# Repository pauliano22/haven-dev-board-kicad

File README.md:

# Haven Dev Board — KiCad Port

> **Current status (as of this commit): fabrication-ready.** Everything
> below this notice describes the *original* EasyEDA→KiCad port and was
> accurate when written, but predates the DRC/routing work that followed —
> it still says "no ERC or DRC has been run," which is no longer true. The
> board has since been rescaled to 73.1×161.1mm, fully routed (219 DRC
> violations remaining, all investigated and non-blocking; 2 cosmetic
> same-net internal BGA pairs unconnected), and DRC-verified via
> `kicad-cli`. See `FABRICATION_GUIDE.md` for current ordering instructions
> and `HAVEN_HARDWARE_REVIEW.md` for the full review trail. The rest of this
> file is kept as-is below for its record of the port's methodology and
> known limitations, most of which are still true (pin electrical types,
> unassigned pins, silkscreen fidelity, etc.) — only the DRC/routing status
> has changed.

A from-scratch KiCad recreation of the stock OpenEarable hardware (the base
Haven is built from), generated programmatically from the real EasyEDA Pro
project data rather than hand-traced from screenshots. This is **not** a
copy-paste of the user's live EasyEDA edits — it's a fresh port of the
*stock* OpenEarable design (`OpenEarable-PCB-main-2.0.epro`), per the
explicit scope agreed before this work started.

Open `kicad/haven_dev_board.kicad_pro` in KiCad. **No KiCad install or
`kicad-cli` was available in the sandbox this was built in — none of this
has been opened in real KiCad, run through ERC, or run through DRC.**
Treat the schematic as a strong first draft and the PCB as a best-effort
faithful port; both need a real review pass before anything is fabricated.
(Superseded — see the notice at the top of this file.)

## What's actually in here

| Section | Confidence | Why |
|---|---|---|
| BOM (89 parts, real values/part numbers) | High | Parsed directly from the `.epro`'s structured JSON, not guessed |
| Digital/power netlist (MCU, power management, flash, SD, USB, IO) | High | Two independent extraction methods agree exactly (see below) |
| Footprints (real pad shapes/sizes/positions) | High | Parsed directly from the real `.efoo` footprint data |
| PCB placement (component X/Y/rotation) | High | This is the **real board's actual placement**, not a guess |
| PCB routing (traces/vias/copper pours) | High for continuity, **unverified for DRC** | Real copper geometry ported directly; never run through a design-rule checker |
| Audio-analog section (ADAU1860 pins, mic, DAC) | Medium | Connectivity is real (same ground-truth source), but pin *electrical roles* (which precise decoupling network, differential pairing, etc.) haven't been cross-checked against the ADAU1860 datasheet |
| RF/antenna, USB signal integrity, any trace-width/impedance intent | **Needs real EE review** | Geometry ported as-is; nothing here was checked against RF/USB layout rules |
| Symbol/footprint graphics (visual appearance) | Cosmetic only | Pins are placed at electrically-correct coordinates but pin-stub direction and body-rectangle sizing are auto-generated, not hand-drawn — expect a plain, boxy look, not the polished look of a hand-drawn library part |

## Data source and methodology

The source is `OpenEarable-PCB-main-2.0.epro`, an EasyEDA Pro export. Unlike
the live `.eprj2` project file (an encrypted SQLite database), a `.epro` is
a zip of plaintext, line-delimited JSON records — genuinely parseable, not
reverse-engineered from pixels.

Two independent data sources were extracted and cross-checked against each
other:

1. **Schematic layer** (`.esch`, `.esym`): component placement, symbol pin
   layouts, and net-label text. EasyEDA's schematic format has no explicit
   netlist — connectivity has to be reconstructed from which pins sit near
   which net-label text. This reconstruction (`extracted/parse_netlist2.py`)
   hit two real bugs before it produced a trustworthy result, both fixed
   and documented in code comments:
   - A naive `name.split(".")[0]` truncated decimal component values
     (e.g. `"2.2uH.1"` → `"2"` instead of `"2.2uH"`), breaking symbol
     lookup for 15 parts. Fixed with a regex that strips only the trailing
     `.N` variant suffix, plus an HTML-entity unescape (BOM value strings
     use a literal `>`, symbol titles use `&gt;`).
   - The nRF5340 module's dedicated DC-DC/decoupling pins (`DECR`, `DCC`,
     `DECD`, `DCCD`, `DCCH` — per the module's own symbol pin names) were
     being swept into unrelated neighboring nets by the proximity-matching
     heuristic, since these pins sit only ~10 units from adjacent signal
     pins on a tight-pitch module. These pins are excluded from proximity
     matching entirely; per the nRF5340 datasheet they only ever connect
     to a local decoupling capacitor, never a routed signal net.

2. **PCB layer** (`.epcb`) — discovered partway through this work, and a
   materially better source: every real pad on the actual manufactured
   board has a `PAD_NET` record giving its **already-resolved** net name
   directly, plus a `COMPONENT` record giving its **real placed position
   and rotation** on the actual board. This is ground truth, not a
   reconstruction. **This is the netlist actually used in the generated
   schematic and PCB** (`extracted/pcb_netlist.json`,
   `extracted/pcb_placement.json`) — it covers ~85% of all pins vs. ~64%
   for the schematic-proximity heuristic, and every net checked against
   both sources agreed exactly (DIN, DOUT, BCLK, LRCLK, FLASH_RESET,
   SD_ENABLE, SCL1/SDA1, and the full GND net all matched).

   The PCB layer also contains real routed copper — 1003 trace segments,
   260 vias, and 6 ground/power copper pours — on a genuine 6-layer
   stackup (confirmed via `LAYER_PHYS` dielectric/copper-thickness
   records): `TOP / prepreg / GND-plane / core / Inner1 / prepreg /
   Inner2 / core / POWER-plane / prepreg / BOTTOM`. All of this routing
   was ported directly rather than re-routed from scratch.

Coordinate systems were independently reverse-engineered and validated for
each domain (schematic-space units are 10 mil per raw grid unit;
PCB-space units are 1 mil per raw unit — confirmed against overall board
span, ~13.5mm × 26.7mm, plausible for a small in-ear wearable). PCB-space
rotation was independently validated against real trace/via endpoints on
two components with 90°/270° rotations (not just 180°, which can't
distinguish rotation direction) — computed pad positions landed within
0.01 raw units (~0.0003mm) of real trace endpoints, confirming standard
CCW rotation with **no mirroring needed**, even for back-side (layer 2)
parts.

The board outline's arc segments (`POLY` records on the OUTLINE layer) use
a `(start, end, sweep-angle)` encoding with no explicit center point. The
center/midpoint formula was derived from scratch and verified in closed
form against two real corner-fillet arcs before being trusted for the
whole outline.

### Coordinate-generation strategy (why the connectivity should be trusted even without ERC)

Every generated symbol instance (schematic) and footprint instance (PCB)
is placed at **rotation zero**, with the component's real rotation baked
directly into each pin/pad's own local coordinate instead. This sidesteps
any uncertainty about whether KiCad's internal rotation transform sign
convention matches EasyEDA's: since only pure translation is asked of
KiCad, and the label/pad-net coordinates are computed with the exact same
Python expression used to place the pin/pad itself, they are numerically
identical by construction — not just "close." The actual rotation-direction
question was still independently resolved and validated (see above); this
strategy just removes it as a second, compounding source of risk.

## Known limitations / simplifications

- ~~**No ERC or DRC has been run.**~~ Superseded — see the notice at the
  top of this file. DRC has since been run extensively via `kicad-cli`
  (219 violations remaining, all investigated; see
  `HAVEN_HARDWARE_REVIEW.md`).
- **POLY-shaped pads** (rare — a few connector pads on J1/CN1 use a custom
  polygon rather than a rectangle/ellipse) are approximated by their
  bounding rectangle, not their exact polygon outline.
- **Via layer spans**: the source data's per-via layer-span field was
  empty for every via found, which is consistent with (but doesn't
  strictly prove) all-through vias. Every via is generated as a full
  F.Cu–B.Cu through via. If any are actually blind/buried, this needs
  correcting.
- **Board stackup thicknesses** are not precisely declared in the
  generated file (KiCad's default 1.6mm/2-layer-style general thickness
  is used) — the *layer names and count* (6 copper layers) are real and
  correct, but exact dielectric thicknesses from the source data were not
  carried through.
- **Silkscreen art, logos, and precise designator label placement** from
  the original board were not ported — only functional copper, pads, and
  the board edge. Reference designators use KiCad's default auto-placed
  text.
- **Pin electrical types** (input/output/power/etc.) are uniformly set to
  "passive" in the generated symbols. This was a deliberate choice: I
  don't have verified per-pin electrical-role data from any datasheet, and
  marking pins with specific types I can't back up would be fabricating
  detail I don't actually have grounds for. This means ERC in KiCad won't
  be meaningful for pin-direction conflicts until someone fills in real
  electrical types from actual datasheets.
- **~15% of pins have no assigned net** (72 of 460 PCB pads; a very
  similar fraction on the schematic side). Spot-checked and these are
  overwhelmingly genuine — reserved MCU pins (the DC-DC pins above),
  unused GPIOs, and connector pins with more physical positions than the
  design actually uses (e.g. CN1 pins 13–24, CARD1 pin 1). They are not
  silently dropped; they're just left unconnected in the generated files
  rather than fabricating a connection.

## A genuine anomaly in the *original* stock design — now resolved

One net in the real board data was literally named `#ERROR` by EasyEDA
itself (confirmed present in `extracted/netlist.json`'s raw source, not
introduced during this port) — it tied together MDBT531 pin 3 (`P1.08`,
a GPIO), Q2 pin 1 (a small MOSFET, `CSD13380F3T`), and U8 pin 1 (a 1MΩ
0201 resistor, despite the "U" designator). EasyEDA just never resolved
a human-readable name for this net.

Traced further and renamed to **`LED_ENABLE`**: R4 (510Ω) and U4 (a real
0201 LED, `XL-0201SURC`, per `HAVEN_BOM.csv`) are also on this net —
3V3 → U4 (LED) → R4 (current-limit) → Q2 (low-side switch to GND), gated
by U8 (1MΩ pulldown, default-off) and driven directly by MDBT531 P1.08.
A straightforward GPIO-controlled indicator LED. Pure rename in both the
schematic and PCB — zero electrical change, verified via DRC diff. The
net also had a genuine small routing gap (Q2's gate pad wasn't
connected to the rest of the net); that's now routed too.

## File layout

```
kicad/
  haven_dev_board.kicad_pro     project file
  haven_dev_board.kicad_sch     schematic (89 components, net labels for connectivity)
  haven_dev_board.kicad_sym     project symbol library (one symbol per component, no sharing)
  haven_dev_board.kicad_pcb     PCB (real placement, real footprints, real routing, real outline)
  footprints.pretty/            33 generated footprints
  sym-lib-table, fp-lib-table   project-local library tables

extracted/                      all extraction/generation scripts + intermediate JSON,
                                 kept for provenance and so the pipeline can be re-run
                                 (e.g. after a schematic re-export) rather than redone by hand
```

## Suggested next steps for a human pass

1. ~~Open in KiCad, run ERC and DRC, see what falls out.~~ Done — see the
   notice at the top of this file and `HAVEN_HARDWARE_REVIEW.md`.
2. Cross-check the ADAU1860 audio-analog section (U15's ~29 unmatched
   pins, mostly clustered here) against the real datasheet.
3. Review U2 (BQ25120A charger) and U6 (BQ27220 fuel gauge) — both have a
   meaningful number of unmatched pins too.
4. ~~Decide whether the `#ERROR` net circuit needs a real name/investigation.~~ Done — see above, now `LED_ENABLE`.
5. If this is meant to diverge from stock OpenEarable (per the earlier
   Gemini-assisted cleanup pass on the user's live EasyEDA project), diff
   this port against that pass and carry over the same changes here.

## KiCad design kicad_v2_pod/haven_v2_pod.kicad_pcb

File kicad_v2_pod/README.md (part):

# Haven v2 behind-the-ear (BTE): schematics

v2's form factor is behind-the-ear (decision 2026-11-03, `HAVEN_V2.md` in the workspace). A pod
behind the ear holds the battery and main board. A fixed thin cable runs over the top of the ear
to a small in-ear unit with the mic, the speaker, the nozzle and the tip.

**Two boards, two KiCad projects:**

| Folder | Board | What's on it |
|---|---|---|
| `kicad_v2_pod/` | Pod board (6-layer, fine pitch) | MDBT53V-1M, nPM1100, ADAU1860 + 24.576 MHz crystal, load switch, status LED, fallback pod mic (U14), charge pads, SWD pads, cable ESD, cable pads |
| `kicad_v2_inear/` | In-ear board (tiny, 2-layer) | SPH0641 mic, 100 nF, 33 Ω series resistor, cable pads, speaker pads |

The boards are fabricated, assembled and laid out separately, and they share nothing but the
cable. Two projects keep each board's DRC rules, stackup and BOM independent: the pod needs the
6-layer fine-pitch rules for the 0.35 mm BGA, while the in-ear board can be a cheap 2-layer
0.6 mm board. A hierarchical single project would force one stackup on both.

**Generated.** `tools/gen_v2_bte_schematic.py` writes both folders. It reuses the parts, symbols
and writer in `tools/gen_v2_schematic.py`, which still generates the single-board pebble design
in `kicad_v2/`. Edit the scripts, not the `.kicad_sch` files.

## Status (2026-11-05)
- Pod: 79 parts, 48 nets. In-ear: 11 parts, 7 nets.
- `kicad-cli sch erc`: **0 violations on both**.
- Exported netlists match the scripts' intended netlists on every net (0 mismatches).
- BOM export works: `kicad_v2_pod/haven_v2_pod_bom.csv`, `kicad_v2_inear/haven_v2_inear_bom.csv`.
- Both boards are laid out (pod: see "Pod layout" below; in-ear: `kicad_v2_inear/README.md`). All symbol pins are "passive", so ERC checks wiring, not driver conflicts.

## Pod layout (2026-11-05)
- 13 × 27 mm, 6 layers, 0.8 mm, outline from haven-hardware `mechanical_cad/v2_bte`.
  Stackup: F.Cu signal | In1 solid GND | In2, In3 signal | In4 signal + GND | B.Cu signal + GND.
- `kicad-cli pcb drc --schematic-parity --severity-all`: **0 violations, 0 unconnected, 0 parity
  issues.** 826 tracks, 143 vias, narrowest track 0.09 mm.
- Rules are JLCPCB's standard 6-layer process: 0.1 mm clearance, 0.09 mm min track, 0.2/0.35 mm
  routing vias, 0.15/0.25 mm vias-in-pad on the codec and PMIC balls and some 0201 GND pads.
  **Order with via-in-pad filled and capped (POFV)**; without it, solder wicks down the ball vias.
- Antenna keep-out: top 3.8 mm, full width, all layers.
- Flow: `tools/gen_v2_pod_pcb.py` (placement, fan-out) → `tools/route_v2_pod_pcb.py`
  (Freerouting) → `tools/fix_v2_pod_pcb.py` → `tools/route_rest_v2_pod.py` (A* for what's left)
  → `tools/rip_reroute_v2_pod.py` (rip up a blocking net and reroute both). The last two steps
  were run by hand on a handful of nets, so re-running the generator does **not** reproduce this
  board; treat `haven_v2_pod.kicad_pcb` as the source from here on.
- Two GND balls have no via of their own and reach GND through a short B.Cu trace to a neighbouring
  GND ball: codec U15 D6 (to D7) and PMIC U2 D5 (to C5). That freed escape routes for SDA1 and
  SHIP_EN.
- Charge contacts: P1 (VBUS) / P2 (GND) are wire-landing pads. The case mates two Ø1.5 mm metal
  contacts in the shell's bottom end, 5.0 mm apart around the magnet; wire each to its pad.
- Before ordering: view it in KiCad's 3D viewer and check the mic port hole (U14) lines up with the
  shell's mic hole; check paste on the bottom-port mic ring as on the in-ear board.

## Cable harness (6 conductors, ~80–100 mm, fixed)
| Pad | Pod net | In-ear net | Signal | Notes |
|---|---|---|---|---|
| W1 | V_LS | V_MIC | Mic supply, 1.8 V | Switched by U3 with the codec |
| W2 | GND | GND | Ground | Lay it between PDM_CLK and PDM_DATA |
| W3 | CBL_PDMCLK | PDM_CLK | PDM clock, codec → mic | 33 Ω series R120 at the pod (the source) |
| W4 | PDMDIN | PDM_DATA | PDM data, mic → codec | 33 Ω series R1 at the mic (the source) |
| W5 | SPK+ | SPK+ | Speaker + | Twist with SPK− |
| W6 | SPK− | SPK− | Speaker − | |

**Cable:** 6 conductors of 38–40 AWG stranded copper (Litz or PTFE-insulated), the speaker pair
twisted, CLK–GND–DATA adjacent, a TPE or PU jacket of about 1.4–1.6 mm, and an aramid strength
member tied off at both ends. Hearing-aid receiver (RIC) wire usually has only 2–4 conductors, so
it isn't enough on its own. A first build can be hand-made from six PTFE wires under heat-shrink.
**Strain relief** is mechanical and belongs to layout and the shell: put the pads in one row at
the board edge where the cable exits, add an anchor slot for the aramid knot, and pot the joint.

## Decisions

**Two mic positions on one PDM pair: in-ear primary, pod fallback** (Paul, 2026-11-04). A mic at
the ear-canal entrance hears the room through the wearer's own outer ear, which keeps natural
direction and pinna cues in hear-through, so the in-ear mic (U13 on the in-ear board) is the
primary. A second SPH0641 on the pod (U14) is the fallback, built into the same pod design so no
second pod board is needed.
- The two mics share PDM_CLK and PDM_DATA on opposite clock edges, set by each mic's SELECT pin.
  From the Knowles SPH0641 datasheet's interface table, SELECT low means the mic drives DATA on
  the falling clock edge, and SELECT high means the rising edge. Each mic leaves the line
  high-impedance on the other half-cycle.
- **In-ear U13: SELECT low = DMIC0.** That's the channel and edge the firmware already uses (same
  as v1/OpenEarable), so the primary needs no firmware change.
- **Pod U14: SELECT high = DMIC1.** The ADAU1860's DMIC01 pin carries both channels on one data
  line, and DMIC0 and DMIC1 route independently: FastDSP inputs 39 and 40, see
  `haven-zephyr-app/docs/fastdsp-program.md`. Using the pod mic is a firmware choice of input,
  DMIC1 instead of DMIC0, in the FastDSP or EQ route. At bring-up, confirm the edge-to-channel
  mapping bits in `DMIC_CTRL2` against the ADAU1860 datasheet.
- Either mic can be left unfitted. If both are fitted, the firmware can pick one or use both.
- Pod mic data goes through its own 33 Ω (R122) onto the shared PDMDIN, and its clock taps PDMCLK
  on the codec side of R120. C116 decouples it.
- **Mechanical note for the pod mic:** it's bottom-port, so drill a hole through the pod board
  under its port. In the pod shell, the port must face outward, away from the head, through a
  sealed channel with a mesh. Keep it away from the charge pads, magnet and cable exit. Acoustic
  feedback to the sealed in-ear speaker should be low with a good tip seal; check it at bring-up.
- The PDM clock is **3.072 MHz** (`DMIC_CTRL1 = 0x33` in `haven-zephyr-app/src/adau1860_control.c`),
  so the bit period is 325 ns. Signal delay along 100 mm of cable is about 0.5 ns, negligible
  for timing.
- Edges a few ns long on 100 mm can ring, so each PDM line has a 33 Ω series resistor at its
  source: R120 for the clock at the codec, R1 for the data at the mic. Each runs next to the
  ground conductor.
- Crosstalk is low risk. The speaker lines carry audio-band signals from a low-impedance driver,
  and their coupling into the PDM lines is millivolts. The PDM edges coupling back into the speaker
  is far above audio.
- **Build variants**, from the same two boards and cable pads:

  | Variant | In-ear unit | Cable | Mic used |
  |---|---|---|---|
  | **6-wire** (primary) | U13, C1 and R1 fitted | All six conductors (W1–W6) | In-ear U13 (DMIC0); pod U14 optional |
  | **2-wire** (fallback) | Speaker only: U13, C1 and R1 not fitted, or just the speaker leads with no in-ear board | Only SPK+/SPK− (W5, W6); W1–W4 left unwired | Pod U14 (DMIC1) |

  The pod board is identical in both variants. In the 2-wire build, the pod still drives
  CBL_PDMCLK onto an unused pad, which is harmless.

**ESD on every cable line leaving the pod** (D2–D6, TI TPD1E05U06DYAR, SOD-523: 5.5 V stand-off,
0.42 pF, ±IEC 61000-4-2 level 4). The cable is touched and the in-ear unit has an open mic port.
D1, the same part, now protects the exposed VBUS charge pad. Pinout from TI SLVSBO7O (rev. O,
2024) Table 4-1: pin 1 I/O, pin 2 GND. The footprint follows TI's DYA0002A land pattern example:
0.4 × 0.67 mm pads, 1.48 mm overall. Check it against TI's drawing once more during layout.

**Battery CP1454 instead of CP1254** (the pod has room). The charge resistor R111 is now 15 kΩ,
for about 40 mA. Nordic's tables give 30 kΩ = 20 mA and 12 kΩ = 50 mA, consistent with
I ≈ 600 V / R at low currents. That's 0.37C for the 108 mAh CP1454 and 0.47C for the 85 mAh
version, so under 0.5C either way: about a 2.5–3 h charge. Termination stays 4.20 V.

**nRF DC/DC inductors not fitted on the first build** (L101/L102 are marked DNP). The module then
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
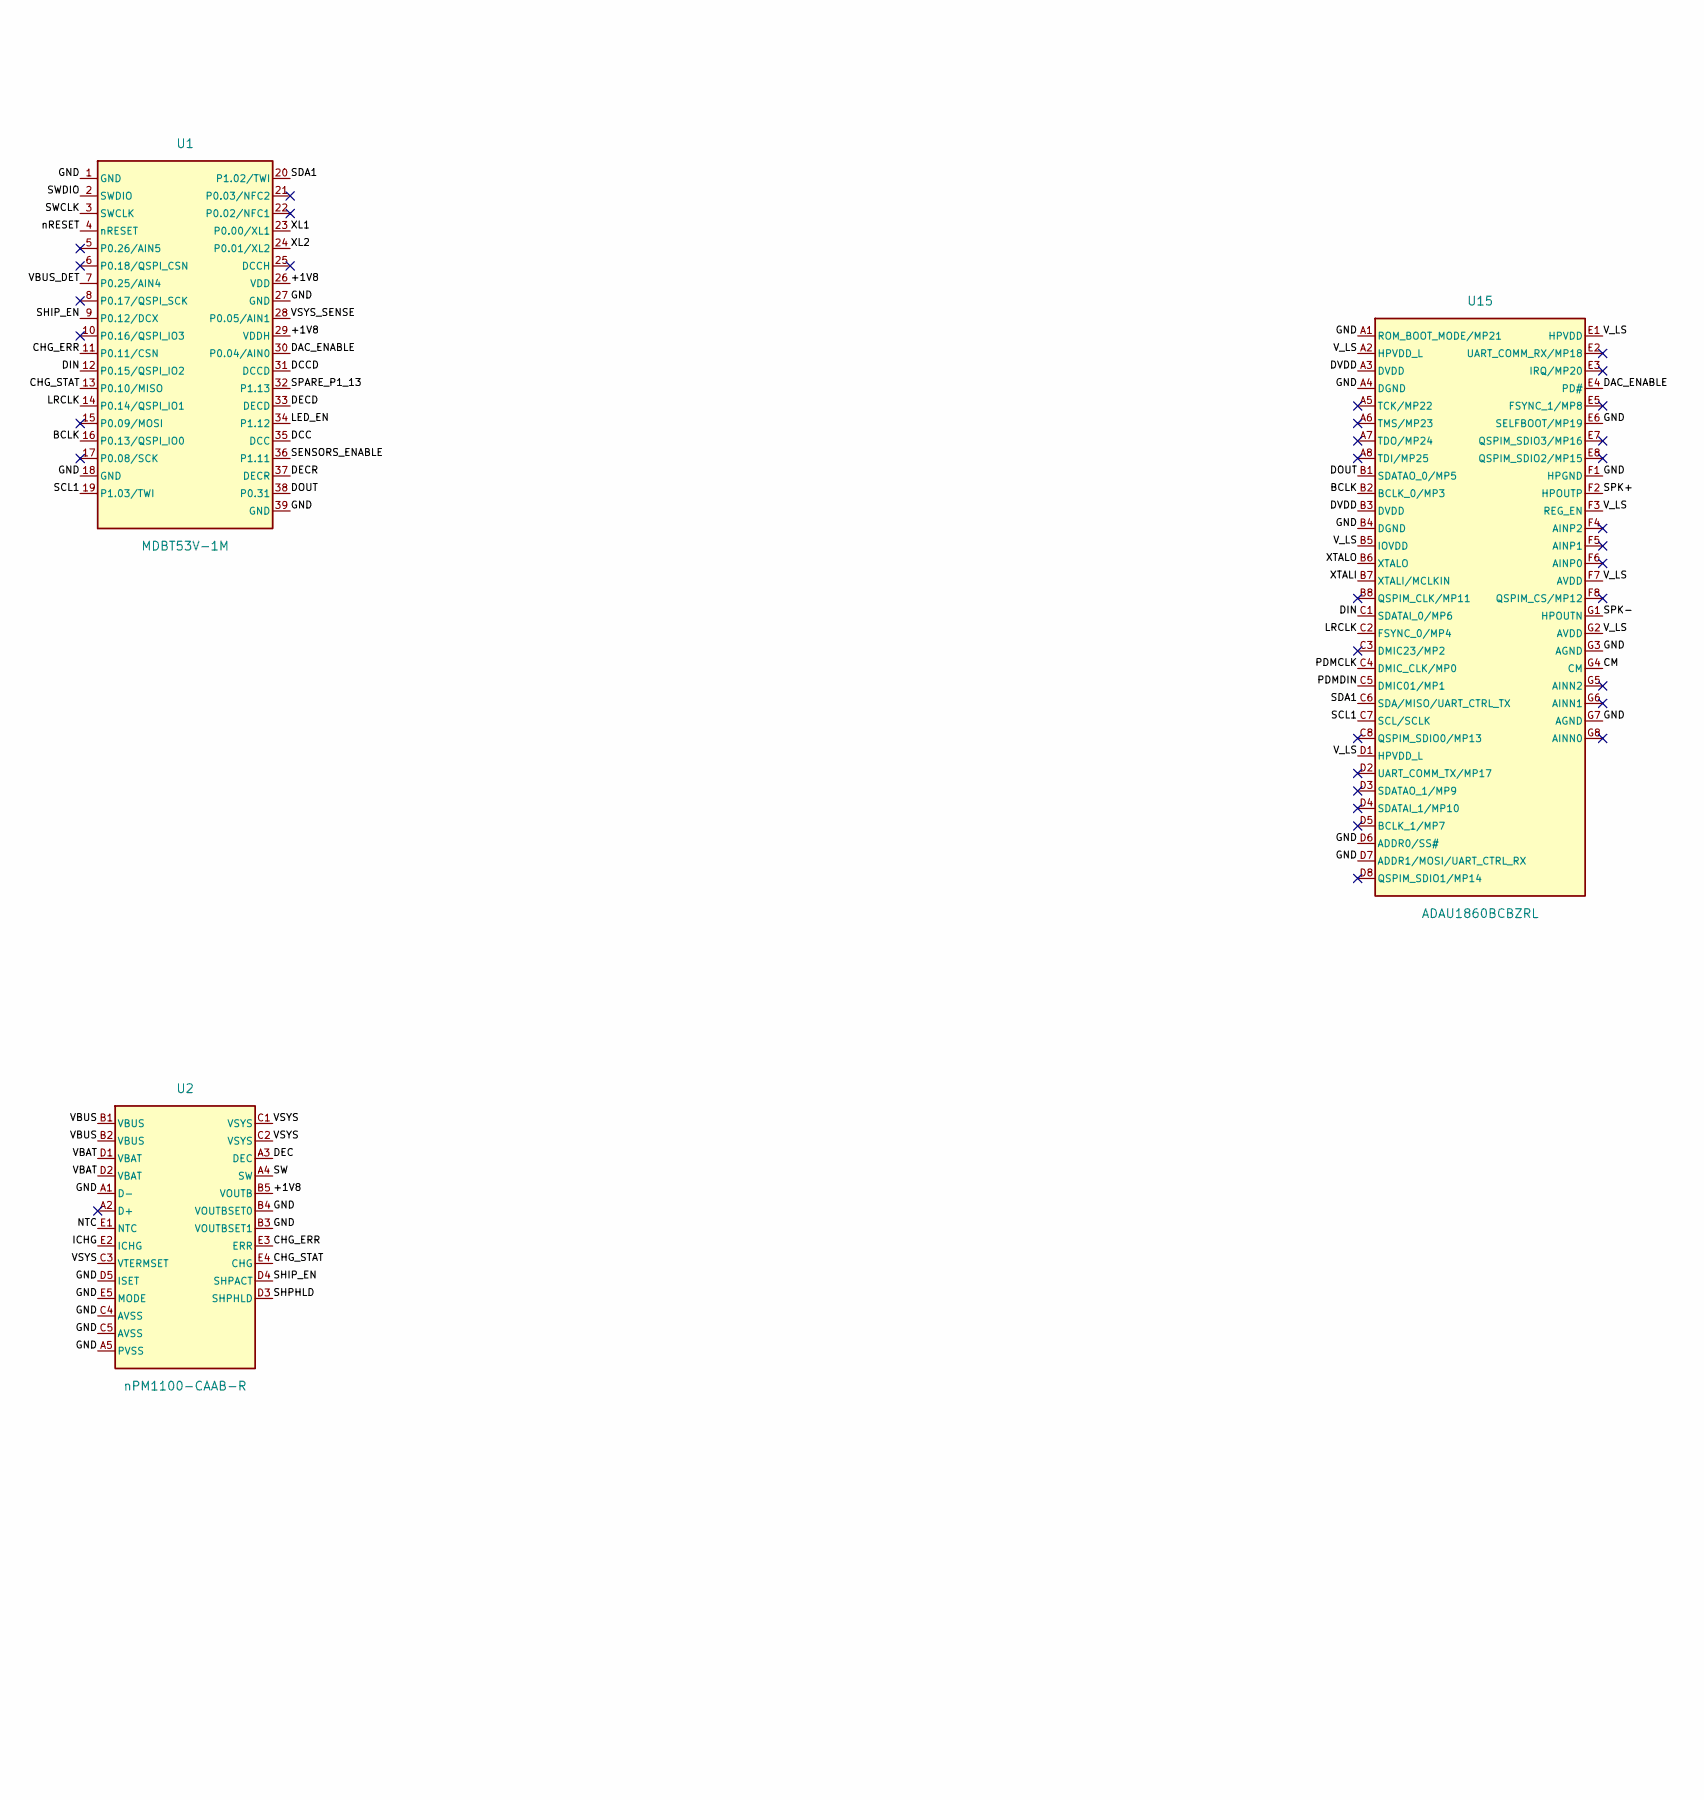
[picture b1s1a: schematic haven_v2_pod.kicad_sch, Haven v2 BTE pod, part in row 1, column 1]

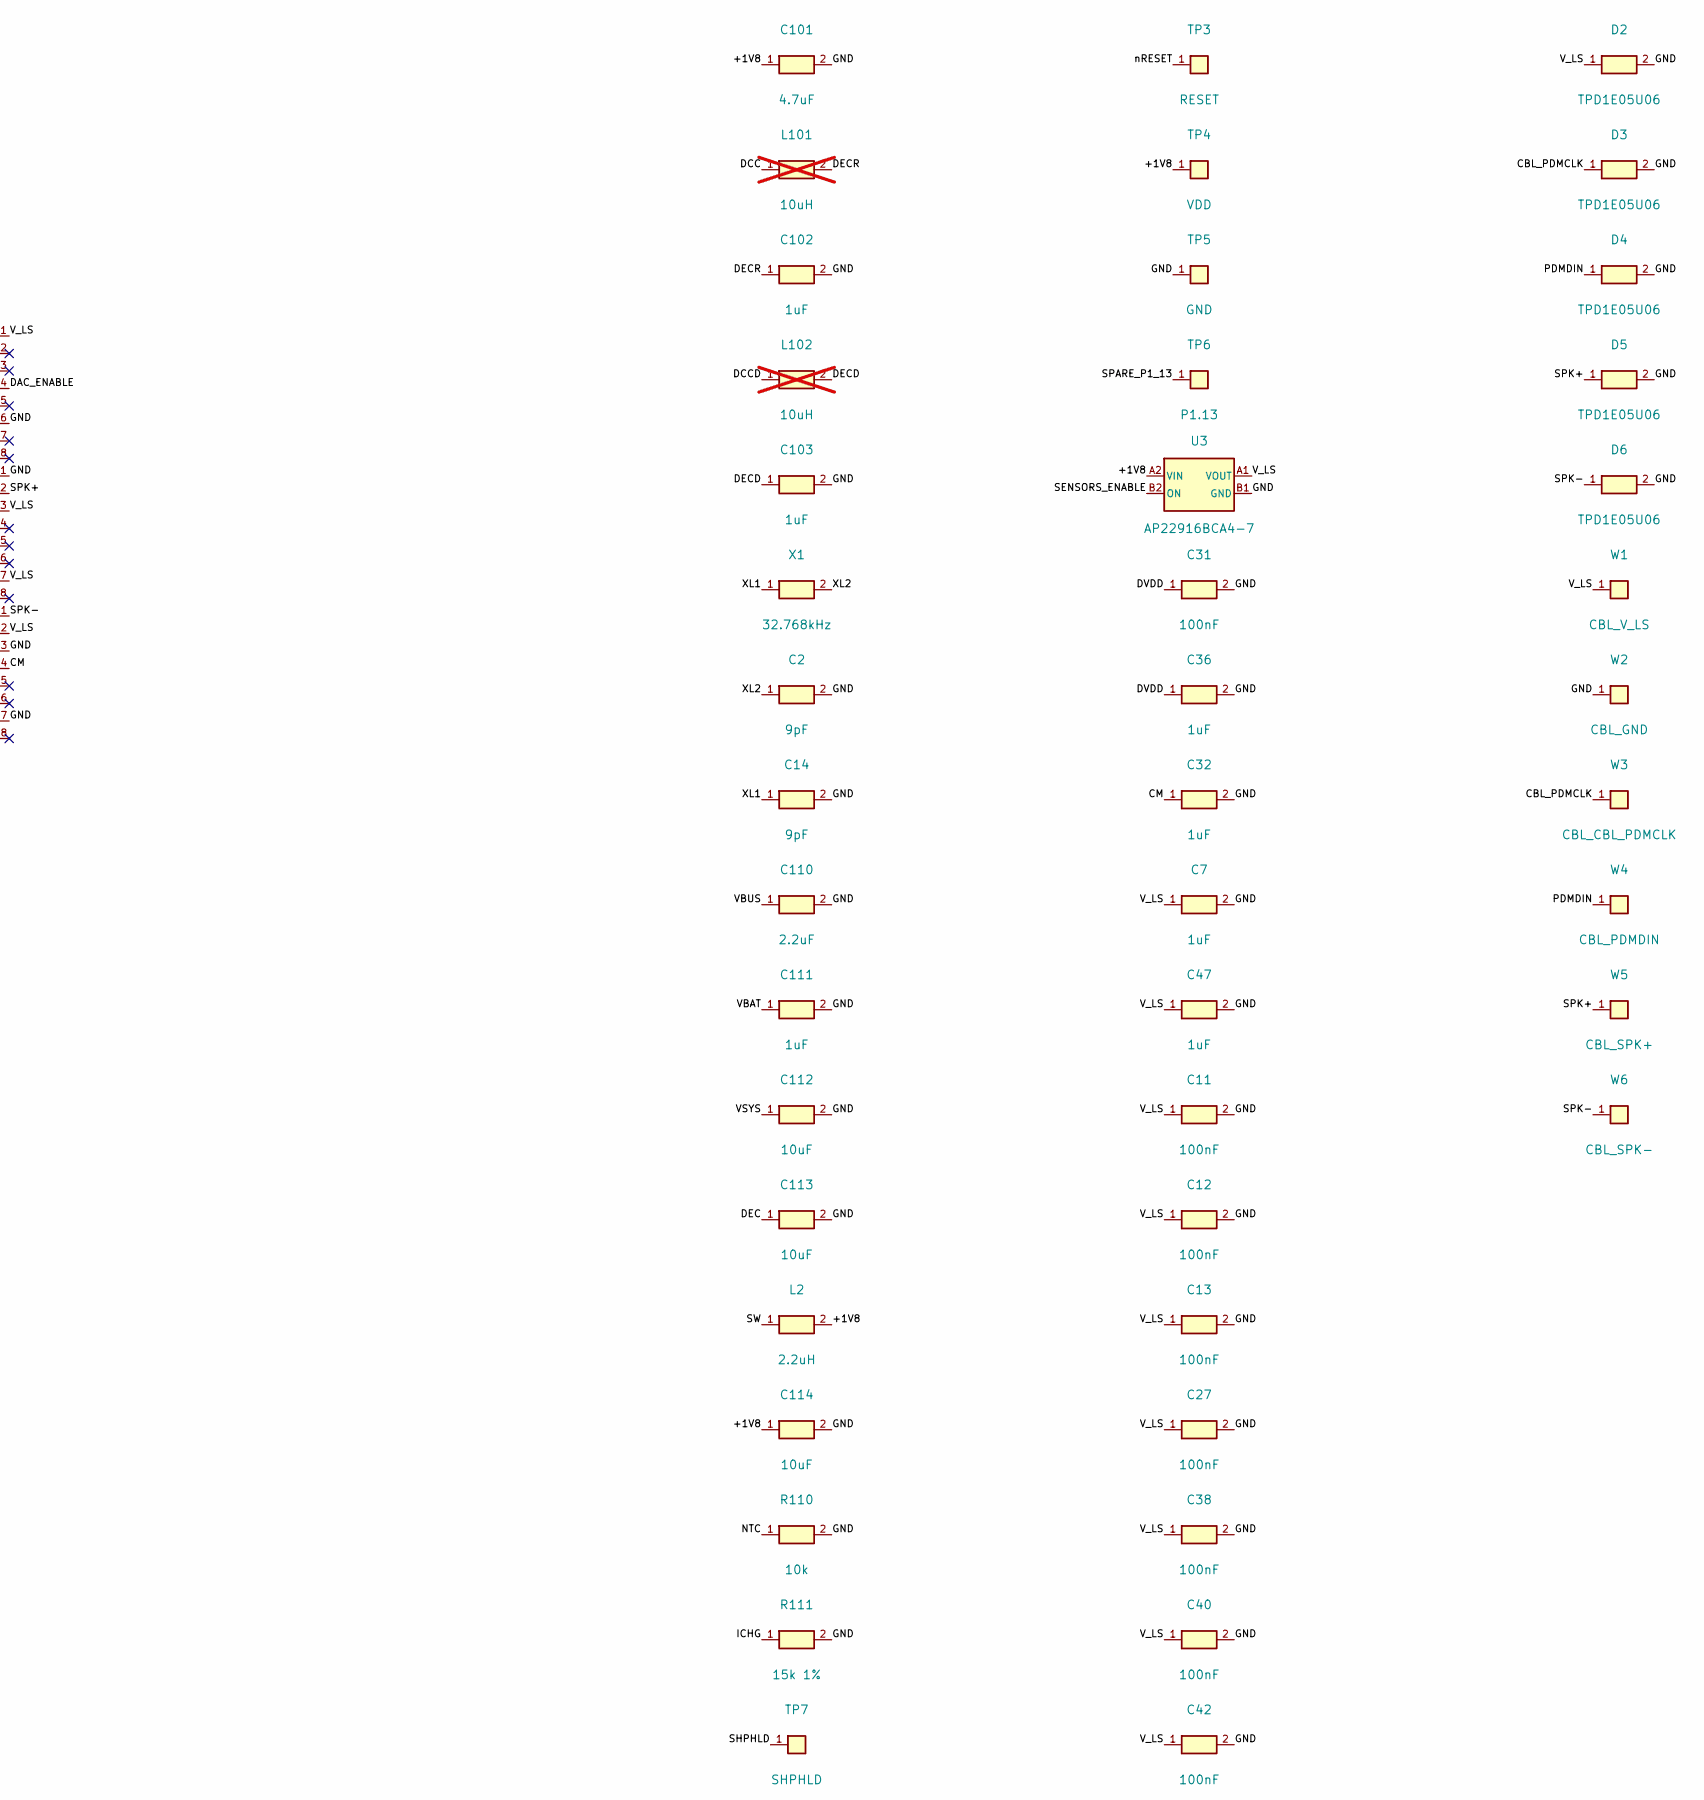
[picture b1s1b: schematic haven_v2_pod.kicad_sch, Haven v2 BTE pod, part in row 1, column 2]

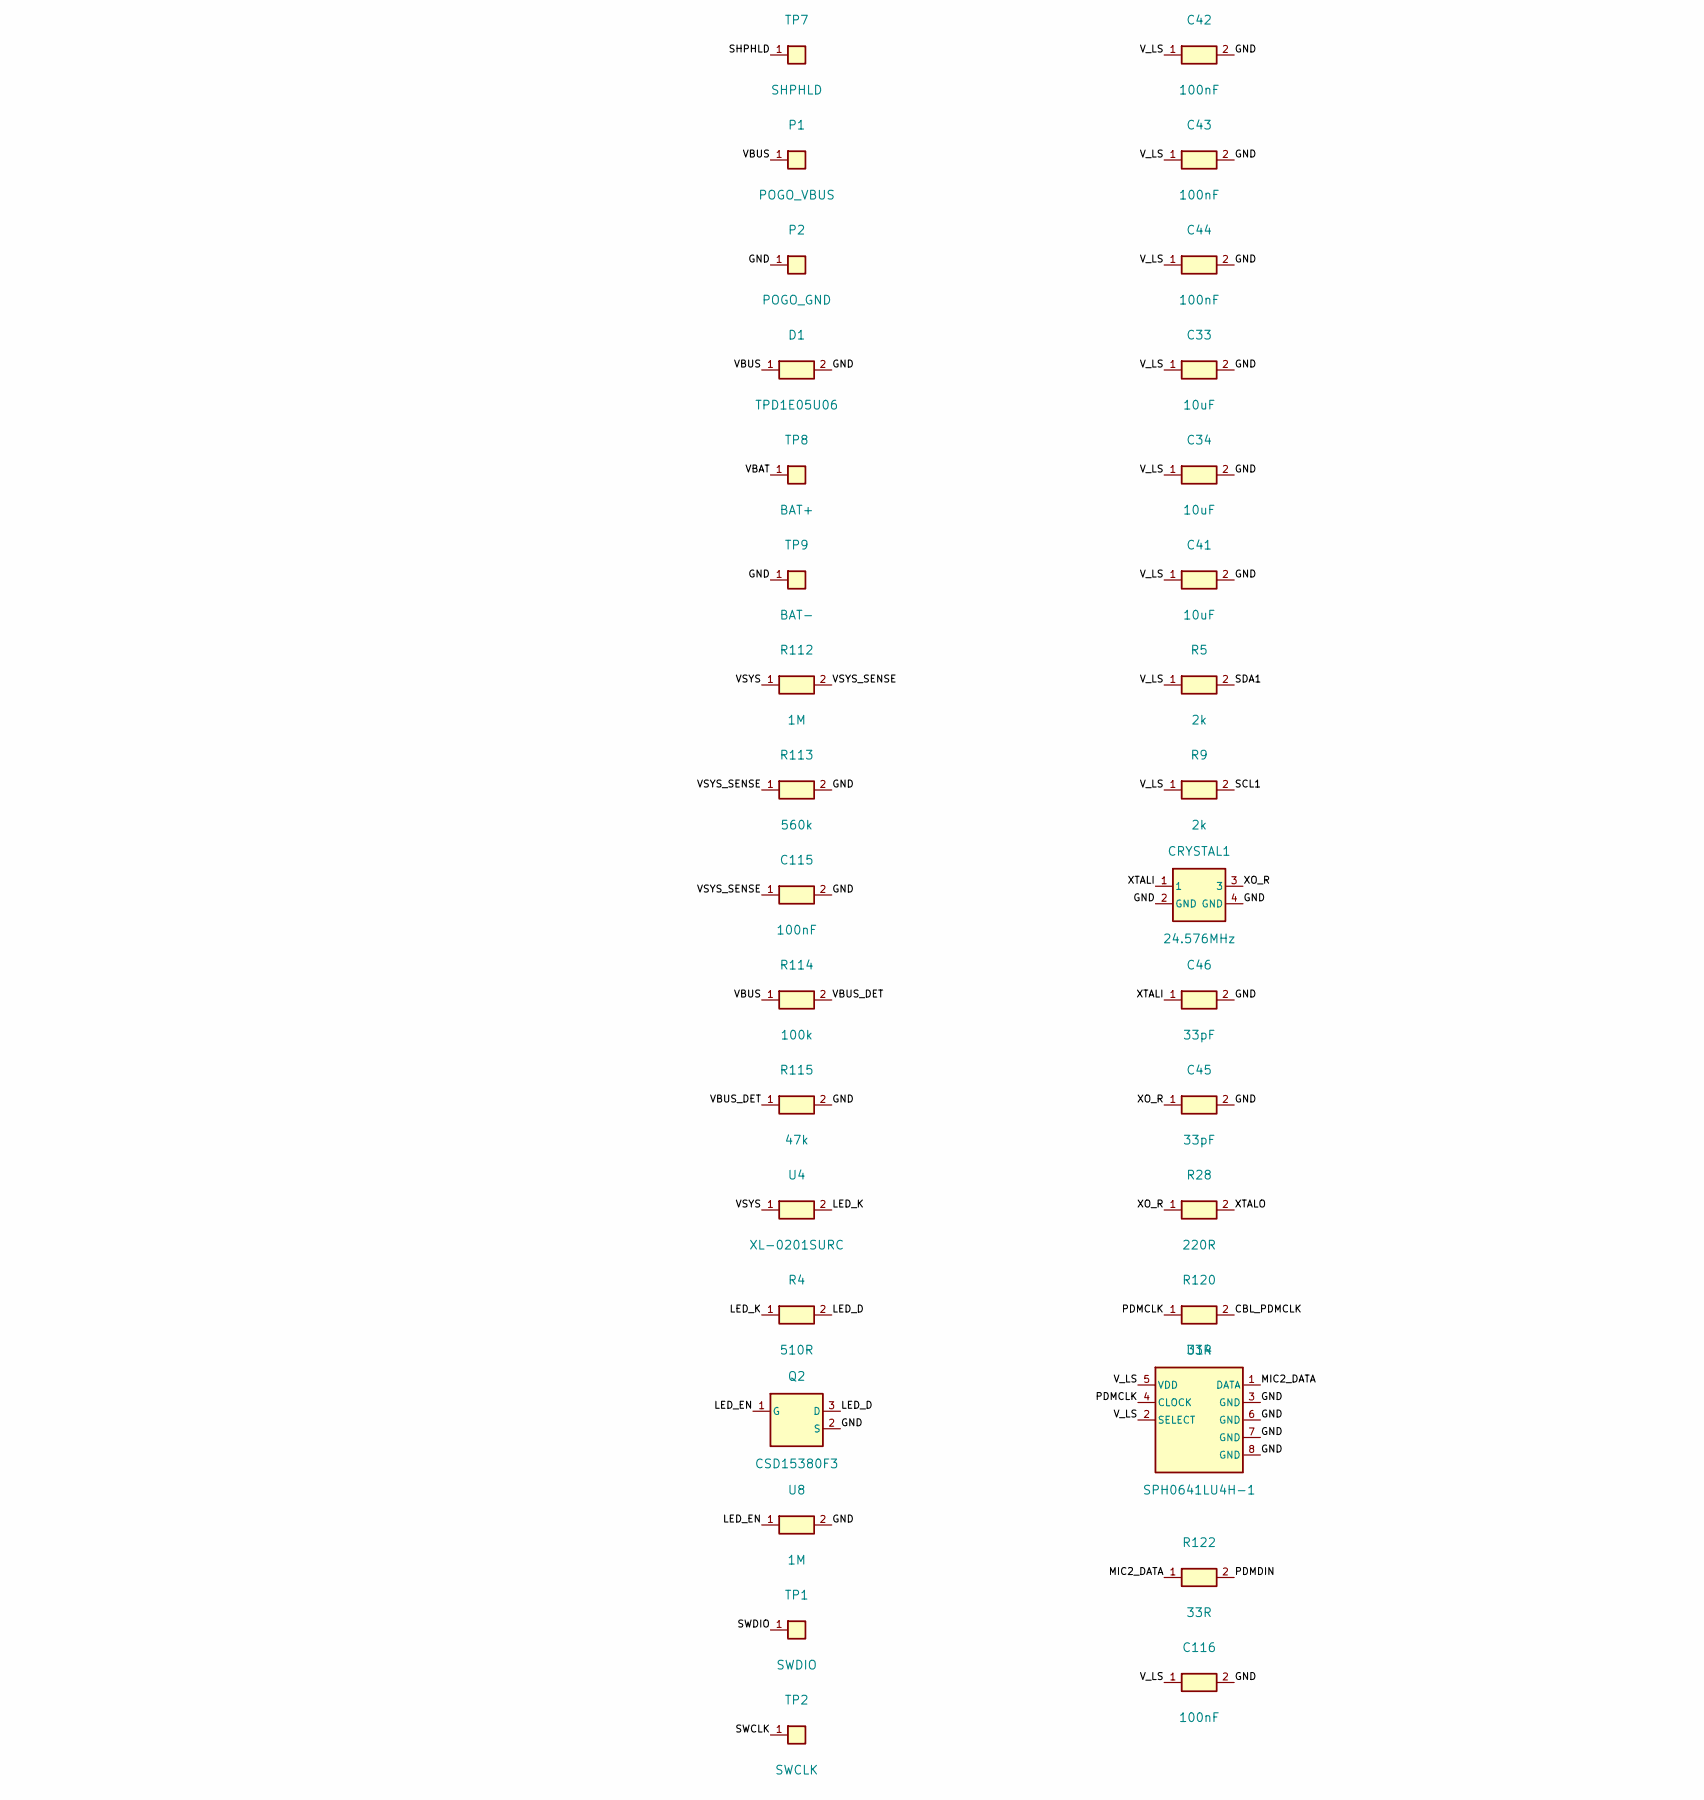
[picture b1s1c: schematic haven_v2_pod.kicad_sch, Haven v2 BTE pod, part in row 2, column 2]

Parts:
C2, C14: 9pF; C0201; MPN CC0201CRNPO9BN9R0; LCSC C277498
C7, C32, C36, C47, C102, C103, C111: 1uF; C0201; MPN GRM033R60J105KEA2D; LCSC C76929
C11, C12, C13, C27, C31, C38, C40, C42, C43, C44, C115, C116: 100nF; C0201; MPN GRM033R60J104KE19D; LCSC C76928
C33, C34, C41, C112, C113, C114: 10uF; C0402; MPN CL05A106MQ5NUNC; LCSC C15525
C45, C46: 33pF; C0201; MPN GRM0335C1H330JA01D; LCSC C76925
C101: 4.7uF; C0402; MPN CL05A475KP5NRNC; LCSC C368809
C110: 2.2uF; C0402; MPN CL05A225KA5NUNC; LCSC C307418
CRYSTAL1: 24.576MHz; CRYSTAL-SMD_4P-L2.0-W1.6-BL_HUAXIN_CN4; MPN CN4024M57620001; LCSC C7294677
D1, D2, D3, D4, D5, D6: TPD1E05U06; D_SOD-523; MPN TPD1E05U06DYAR; LCSC C3702980
L2: 2.2uH; L0402; MPN MLZ1005M2R2WT000; LCSC C383389
L101, L102: 10uH; L0402; not fitted
P1: POGO_VBUS; PogoPad_1.6
P2: POGO_GND; PogoPad_1.6
Q2: CSD15380F3; PICOSTAR-3_L0.7-W0.6-P0.40-TL; MPN CSD15380F3; LCSC C529568
R4: 510R; R0201; MPN WR02X511JAL; LCSC C180335
R5, R9: 2k; R0201; MPN CR0201JH0202G; LCSC C100158
R28: 220R; R0201; MPN RC0201FR-07220RL; LCSC C274342
R110: 10k; R0201; MPN RC0201FR-0710KL; LCSC C106225
R111: 15k 1%; R0201; MPN 0201WMF1502TEE; LCSC C473452
R112: 1M; R0201; MPN CQ01WMJ0105TEE; LCSC C5151554
R113: 560k; R0201; MPN RC0201FR-07560KL; LCSC C295807
R114: 100k; R0201; MPN RC0201FR-07100KL; LCSC C106224
R115: 47k; R0201; MPN RC0201FR-0747KL; LCSC C138139
R120, R122: 33R; R0201; MPN ERJ1GNF33R0C; LCSC C717007
TP1: SWDIO; TestPad_0.8
TP2: SWCLK; TestPad_0.8
TP3: RESET; TestPad_0.8
TP4: VDD; TestPad_0.8
TP5: GND; TestPad_0.8
TP6: P1.13; TestPad_0.8
TP7: SHPHLD; TestPad_0.8
TP8: BAT+; Pad_1.2
TP9: BAT-; Pad_1.2
U1: MDBT53V-1M; MPN MDBT53V-1M
U2: nPM1100-CAAB-R; WLCSP-25_2.075x2.075_P0.4; MPN NPM1100-CAAB-R
U3: AP22916BCA4-7; X1-WLB0808-4_L0.8-W0.8-P0.40-TL; MPN AP22916BCA4-7; LCSC C5244375
U4: XL-0201SURC; LED-SMD_L0.65-W0.35-P0.41_XL-0201SURC; MPN XL-0201SURC; LCSC C3646923
U8: 1M; R0201; MPN CQ01WMJ0105TEE; LCSC C5151554
U14: SPH0641LU4H-1; MIC-SMD_5P_L3.5-W2.7-P0.82_SPH0641LU4H-1; MPN SPH0641LU4H-1; LCSC C2879853
U15: ADAU1860BCBZRL; BGA-56_L3.0-W2.7-P0.35-R8-C7-TL; MPN ADAU1860BCBZRL; LCSC C17592940
W1: CBL_V_LS; WirePad_0.8
W2: CBL_GND; WirePad_0.8
W3: CBL_CBL_PDMCLK; WirePad_0.8
W4: CBL_PDMDIN; WirePad_0.8
W5: CBL_SPK+; WirePad_0.8
W6: CBL_SPK-; WirePad_0.8
X1: 32.768kHz; FC-135R_L3.2-W1.5; MPN Q13FC1350000200; LCSC C48615

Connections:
/+1V8: C101.1, C114.1, L2.2, TP4.1, U1.26 (VDD), U1.29 (VDDH), U2.B5 (VOUTB), U3.A2 (VIN)
/BCLK: U1.16 (P0.13/QSPI_IO0), U15.B2 (BCLK_0/MP3)
/CBL_PDMCLK: D3.1 (K), R120.2, W3.1
/CHG_ERR: U1.11 (P0.11/CSN), U2.E3 (ERR)
/CHG_STAT: U1.13 (P0.10/MISO), U2.E4 (CHG)
/CM: C32.1, U15.G4 (CM)
/DAC_ENABLE: U1.30 (P0.04/AIN0), U15.E4 (PD#)
/DCC: L101.1, U1.35 (DCC)
/DCCD: L102.1, U1.31 (DCCD)
/DEC: C113.1, U2.A3 (DEC)
/DECD: C103.1, L102.2, U1.33 (DECD)
/DECR: C102.1, L101.2, U1.37 (DECR)
/DIN: U1.12 (P0.15/QSPI_IO2), U15.C1 (SDATAI_0/MP6)
/DOUT: U1.38 (P0.31), U15.B1 (SDATAO_0/MP5)
/DVDD: C31.1, C36.1, U15.A3 (DVDD), U15.B3 (DVDD)
/GND: C2.2, C7.2, C11.2, C12.2, C13.2, C14.2, C27.2, C31.2, C32.2, C33.2, C34.2, C36.2, C38.2, C40.2, C41.2, C42.2, C43.2, C44.2, C45.2, C46.2, C47.2, C101.2, C102.2, C103.2, C110.2, C111.2, C112.2, C113.2, C114.2, C115.2, C116.2, CRYSTAL1.2 (GND), CRYSTAL1.4 (GND), D1.2 (A), D2.2 (A), D3.2 (A), D4.2 (A), D5.2 (A), D6.2 (A), P2.1, Q2.2 (S), R110.2, R111.2, R113.2, R115.2, TP5.1, TP9.1, U1.1 (GND), U1.18 (GND), U1.27 (GND), U1.39 (GND), U2.A1 (D-), U2.A5 (PVSS), U2.B3 (VOUTBSET1), U2.B4 (VOUTBSET0), U2.C4 (AVSS), U2.C5 (AVSS), U2.D5 (ISET), U2.E5 (MODE), U3.B1 (GND), U8.2, U14.3 (GND), U14.6 (GND), U14.7 (GND), U14.8 (GND), U15.A1 (ROM_BOOT_MODE/MP21), U15.A4 (DGND), U15.B4 (DGND), U15.D6 (ADDR0/SS#), U15.D7 (ADDR1/MOSI/UART_CTRL_RX), U15.E6 (SELFBOOT/MP19), U15.F1 (HPGND), U15.G3 (AGND), U15.G7 (AGND), W2.1
/ICHG: R111.1, U2.E2 (ICHG)
/LED_D: Q2.3 (D), R4.2
/LED_EN: Q2.1 (G), U1.34 (P1.12), U8.1
/LED_K: R4.1, U4.2 (K)
/LRCLK: U1.14 (P0.14/QSPI_IO1), U15.C2 (FSYNC_0/MP4)
/MIC2_DATA: R122.1, U14.1 (DATA)
/NTC: R110.1, U2.E1 (NTC)
/PDMCLK: R120.1, U14.4 (CLOCK), U15.C4 (DMIC_CLK/MP0)
/PDMDIN: D4.1 (K), R122.2, U15.C5 (DMIC01/MP1), W4.1
/SCL1: R9.2, U1.19 (P1.03/TWI), U15.C7 (SCL/SCLK)
/SDA1: R5.2, U1.20 (P1.02/TWI), U15.C6 (SDA/MISO/UART_CTRL_TX)
/SENSORS_ENABLE: U1.36 (P1.11), U3.B2 (ON)
/SHIP_EN: U1.9 (P0.12/DCX), U2.D4 (SHPACT)
/SHPHLD: TP7.1, U2.D3 (SHPHLD)
/SPARE_P1_13: TP6.1, U1.32 (P1.13)
/SPK+: D5.1 (K), U15.F2 (HPOUTP), W5.1
/SPK-: D6.1 (K), U15.G1 (HPOUTN), W6.1
/SW: L2.1, U2.A4 (SW)
/SWCLK: TP2.1, U1.3 (SWCLK)
/SWDIO: TP1.1, U1.2 (SWDIO)
/VBAT: C111.1, TP8.1, U2.D1 (VBAT), U2.D2 (VBAT)
/VBUS: C110.1, D1.1 (K), P1.1, R114.1, U2.B1 (VBUS), U2.B2 (VBUS)
/VBUS_DET: R114.2, R115.1, U1.7 (P0.25/AIN4)
/VSYS: C112.1, R112.1, U2.C1 (VSYS), U2.C2 (VSYS), U2.C3 (VTERMSET), U4.1 (A)
/VSYS_SENSE: C115.1, R112.2, R113.1, U1.28 (P0.05/AIN1)
/V_LS: C7.1, C11.1, C12.1, C13.1, C27.1, C33.1, C34.1, C38.1, C40.1, C41.1, C42.1, C43.1, C44.1, C47.1, C116.1, D2.1 (K), R5.1, R9.1, U3.A1 (VOUT), U14.2 (SELECT), U14.5 (VDD), U15.A2 (HPVDD_L), U15.B5 (IOVDD), U15.D1 (HPVDD_L), U15.E1 (HPVDD), U15.F3 (REG_EN), U15.F7 (AVDD), U15.G2 (AVDD), W1.1
/XL1: C14.1, U1.23 (P0.00/XL1), X1.1
/XL2: C2.1, U1.24 (P0.01/XL2), X1.2
/XO_R: C45.1, CRYSTAL1.3, R28.1
/XTALI: C46.1, CRYSTAL1.1, U15.B7 (XTALI/MCLKIN)
/XTALO: R28.2, U15.B6 (XTALO)
/nRESET: TP3.1, U1.4 (nRESET)

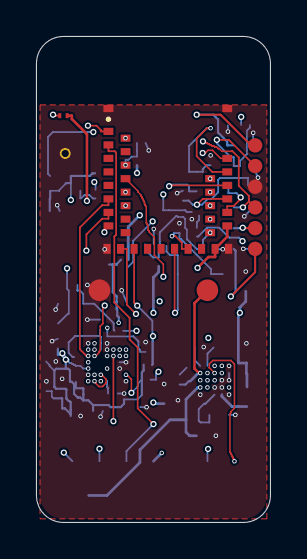
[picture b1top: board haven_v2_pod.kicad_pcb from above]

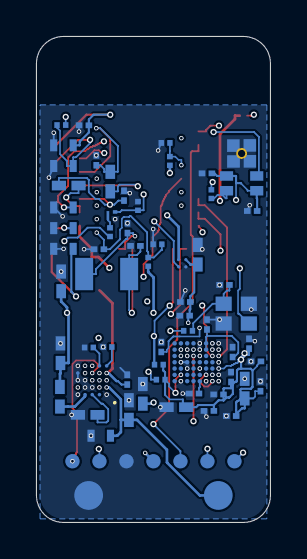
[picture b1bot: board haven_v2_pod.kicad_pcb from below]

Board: 6 copper layers, 13.0 x 27.0 mm, 79 parts (69 on the bottom side), 48 nets.

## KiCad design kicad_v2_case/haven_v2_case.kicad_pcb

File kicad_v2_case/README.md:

# Haven v2 BTE charging case: schematic

Generated by `tools/gen_v2_case_schematic.py` (edit the script, not the `.kicad_sch`).
Charge-only, no microcontroller. 26 parts, 11 nets. `kicad-cli sch erc`: 0 violations.

```
USB-C (5 V sink: CC1/CC2 5.1k) ── MCP73831 charger, 250 mA ── ~800 mAh 1S LiPo (with PCM), JST-SH
                                       └─ red LED: on while charging
LiPo ── TPS61023 boost, 4.95 V, always on ── pogo pins: L pod (VBUS, GND), R pod (VBUS, GND)
```

## Decisions
- **No IP5306.** It switches its 5 V output off below ~45 mA, and two charging pods (~40 mA
  each, falling as they fill) sit right at that edge.
- **No BQ25619.** Its 5 V boost needs an I2C write to enable, so it needs a microcontroller.
- **Charger:** MCP73831 (LCSC C424093). The TP4054 has the same pinout and the same
  ~1000/R(kΩ) mA rule, so it is a drop-in if MCP73831 stock is short. R3 = 4.02k gives ~250 mA.
- **Boost:** TI TPS61023 (LCSC C1852149), values from its datasheet (SLVSF14B, Figure 8-1):
  1 µH, 10 µF in, 2 × 22 µF out, 732k/100k → 4.95 V. EN is tied to VIN, so it is always on:
  20–30 µA standby, about 3 years on a full 800 mAh cell. A short on the pogo pins folds the
  output back to ~350 mA, and it restarts when the short is released (datasheet 7.3.7).
- **Per-pod current:** each pod's nPM1100 limits itself to 100 mA, so no per-pod switch.
- **Battery:** 800 mAh is about 3 full recharges of both pods (2 × ~100 mAh per recharge,
  ~85% boost efficiency, plus margin). Buy a cell **with** a protection board (PCM); the board has
  no undervoltage cut-off of its own.
- **Pogo pins:** 2 per pod, **5.0 mm apart**, centred on the pod's 3 mm magnet. They mate the two
  Ø1.5 mm contacts in the pod shell's bottom end (haven-hardware `v2_bte`, PAD_PITCH 2.5 mm), not
  the board pads directly: on the first build each shell contact is a short wire to P1/P2.
  The footprint is a 2.2 mm round seat for a 2.0 mm-base SMD spring pin; the actual part is open.
- ESD (TPD1E05U06, same as the pod) on USB VBUS and on the pogo VBUS rail.

## Layout (2026-11-05)
- 44 × 15.5 mm, 2 layers, 1.0 mm, all parts on top. Outline and pin positions come from
  haven-hardware `mechanical_cad/v2_bte/case.json` (the board sits on the case's bottom plate
  under the pods).
- `kicad-cli pcb drc --schematic-parity --severity-all`: **0 violations, 0 unconnected, 0 parity
  issues.** JLCPCB standard 2-layer rules (0.15 mm clearance, 0.6/0.3 mm vias).
- Flow: `tools/gen_v2_case_schematic.py` → `tools/gen_v2_case_pcb.py` (placement, the SW trace,
  pours) → `tools/route_v2_case_pcb.py` (Freerouting) → `tools/stitch_v2_case_pcb.py` (GND
  stitching). One GND island (under R2) got a via by hand after stitching.
- The spring pins sit exactly under the pod contacts. USB-C (J1) is at x = −2 mm with its mouth
  flush with the back edge, and the charge LED (D2) is at the back edge behind the case's light hole.
- Boost layout: U2's SW pin sits straight under L1's SW pad (0.35 mm trace, ~1.3 mm long). The
  output caps are on the side the VOUT pin faces, and the input cap is beside L1's VBAT pad.
- Spring pins: candidate Kinghelm KH-PG2011005-DZ (LCSC C2842935), SMD, 11 mm free, 2 mm base, on
  the 2.2 mm round seat. The case puts the board top 10.0 mm below the pod contacts (~1 mm of
  compression); the stroke isn't published, so measure a real pin and adjust `POGO_WORK_H` in
  haven-hardware `case.py`.

## Firmware impact
- Pods see 5 V on VBUS whenever they sit in the case (VBUS_DET). The pod firmware should drop to
  its lowest-power state there (no advertising), or it will drain the case battery.

## Open
1. Pogo pin: confirm KH-PG2011005-DZ's stroke and base land pattern on a real part.
2. (Done 2026-11-05: every placed part has a verified LCSC number.)

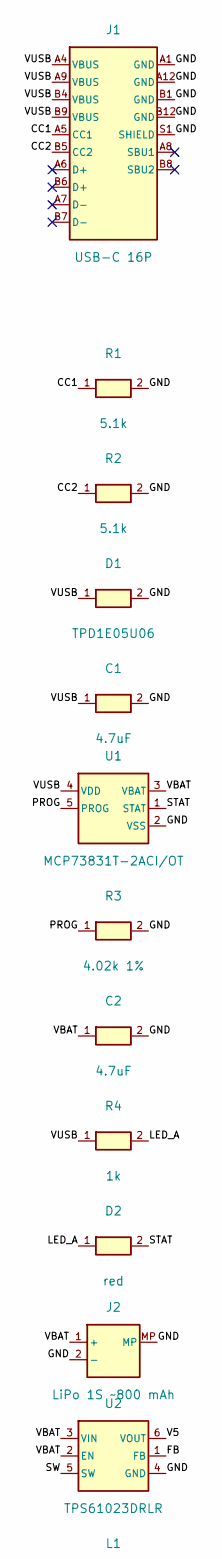
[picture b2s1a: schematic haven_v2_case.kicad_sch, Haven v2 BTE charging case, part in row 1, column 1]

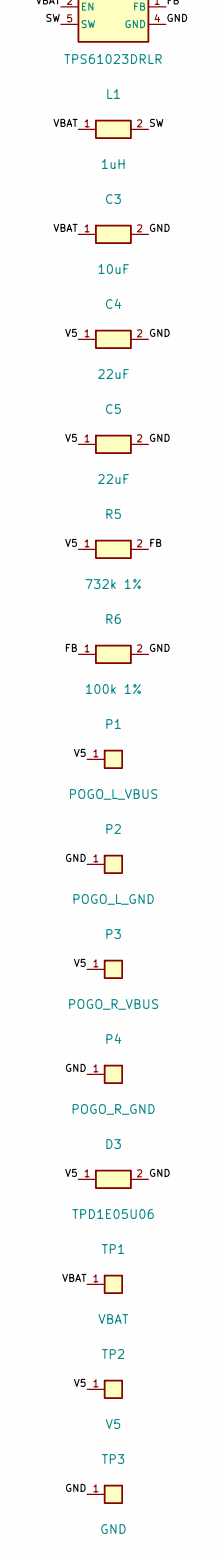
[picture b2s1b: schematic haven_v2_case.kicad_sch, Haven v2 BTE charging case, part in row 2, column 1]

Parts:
C1, C2: 4.7uF; C_0603_1608Metric
C3: 10uF; C_0805_2012Metric
C4, C5: 22uF; C_0805_2012Metric
D1, D3: TPD1E05U06; D_SOD-523; MPN TPD1E05U06DYAR; LCSC C3702980
D2: red; LED_0603_1608Metric
J1: USB-C 16P; USB_C_Receptacle_HRO_TYPE-C-31-M-12; MPN TYPE-C-31-M-12; LCSC C165948
J2: LiPo 1S ~800 mAh; JST_SH_SM02B-SRSS-TB_1x02-1MP_P1.00mm_Horizontal
L1: 1uH; L_1008_2520Metric
P1: POGO_L_VBUS; PogoPin_SMD_D2.0
P2: POGO_L_GND; PogoPin_SMD_D2.0
P3: POGO_R_VBUS; PogoPin_SMD_D2.0
P4: POGO_R_GND; PogoPin_SMD_D2.0
R1, R2: 5.1k; R_0402_1005Metric
R3: 4.02k 1%; R_0402_1005Metric
R4: 1k; R_0402_1005Metric
R5: 732k 1%; R_0402_1005Metric
R6: 100k 1%; R_0402_1005Metric
TP1: VBAT; Pad_1.2
TP2: V5; Pad_1.2
TP3: GND; Pad_1.2
U1: MCP73831T-2ACI/OT; SOT-23-5; MPN MCP73831T-2ACI/OT; LCSC C424093
U2: TPS61023DRLR; SOT-563; MPN TPS61023DRLR; LCSC C1852149

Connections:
/CC1: J1.A5 (CC1), R1.1
/CC2: J1.B5 (CC2), R2.1
/FB: R5.2, R6.1, U2.1 (FB)
/GND: C1.2, C2.2, C3.2, C4.2, C5.2, D1.2 (A), D3.2 (A), J1.A1 (GND), J1.A12 (GND), J1.B1 (GND), J1.B12 (GND), J1.S1 (SHIELD), J2.2 (-), J2.MP, P2.1, P4.1, R1.2, R2.2, R3.2, R6.2, TP3.1, U1.2 (VSS), U2.4 (GND)
/LED_A: D2.1 (A), R4.2
/PROG: R3.1, U1.5 (PROG)
/STAT: D2.2 (K), U1.1 (STAT)
/SW: L1.2, U2.5 (SW)
/V5: C4.1, C5.1, D3.1 (K), P1.1, P3.1, R5.1, TP2.1, U2.6 (VOUT)
/VBAT: C2.1, C3.1, J2.1 (+), L1.1, TP1.1, U1.3 (VBAT), U2.2 (EN), U2.3 (VIN)
/VUSB: C1.1, D1.1 (K), J1.A4 (VBUS), J1.A9 (VBUS), J1.B4 (VBUS), J1.B9 (VBUS), R4.1, U1.4 (VDD)

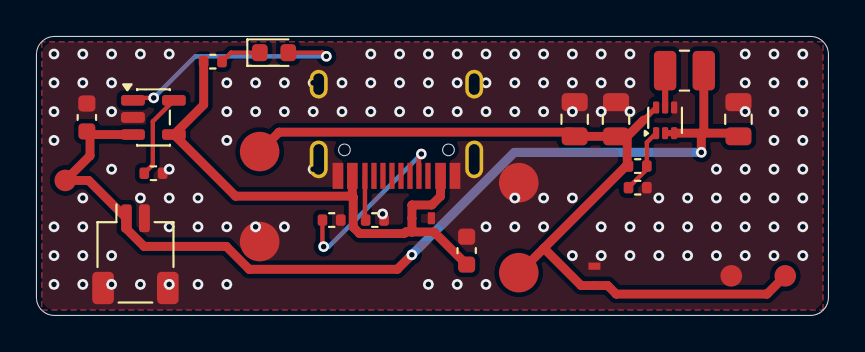
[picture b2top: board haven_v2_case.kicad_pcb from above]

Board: 2 copper layers, 44.0 x 15.5 mm, 26 parts (0 on the bottom side), 11 nets.

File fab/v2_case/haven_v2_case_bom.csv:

Comment,Designator,Footprint,Manufacturer Part,LCSC Part #
4.7uF,"C1,C2",C_0603_1608Metric,CL10A475KO8NNNC,C19666
10uF,C3,C_0805_2012Metric,CL21A106KAYNNNE,C15850
22uF,"C4,C5",C_0805_2012Metric,CL21A226MAQNNNE,C45783
TPD1E05U06,"D1,D3",D_SOD-523,TPD1E05U06DYAR,C3702980
red,D2,LED_0603_1608Metric,KT-0603R,C2286
USB-C 16P,J1,USB_C_Receptacle_HRO_TYPE-C-31-M-12,TYPE-C-31-M-12,C165948
LiPo 1S ~800 mAh,J2,JST_SH_SM02B-SRSS-TB_1x02-1MP_P1.00mm_Horizontal,SM02B-SRSS-TB(LF)(SN),C160402
1uH,L1,L_1008_2520Metric,MPIH252010-1R0M-LF,C490445
5.1k,"R1,R2",R_0402_1005Metric,0402WGF5101TCE,C25905
4.02k 1%,R3,R_0402_1005Metric,CRCW04024K02FKED,C844509
1k,R4,R_0402_1005Metric,0402WGF1001TCE,C11702
732k 1%,R5,R_0402_1005Metric,0402WGF7323TCE,C27016
100k 1%,R6,R_0402_1005Metric,0402WGF1003TCE,C25741
MCP73831T-2ACI/OT,U1,SOT-23-5,MCP73831T-2ACI/OT,C424093
TPS61023DRLR,U2,SOT-563,TPS61023DRLR,C1852149
